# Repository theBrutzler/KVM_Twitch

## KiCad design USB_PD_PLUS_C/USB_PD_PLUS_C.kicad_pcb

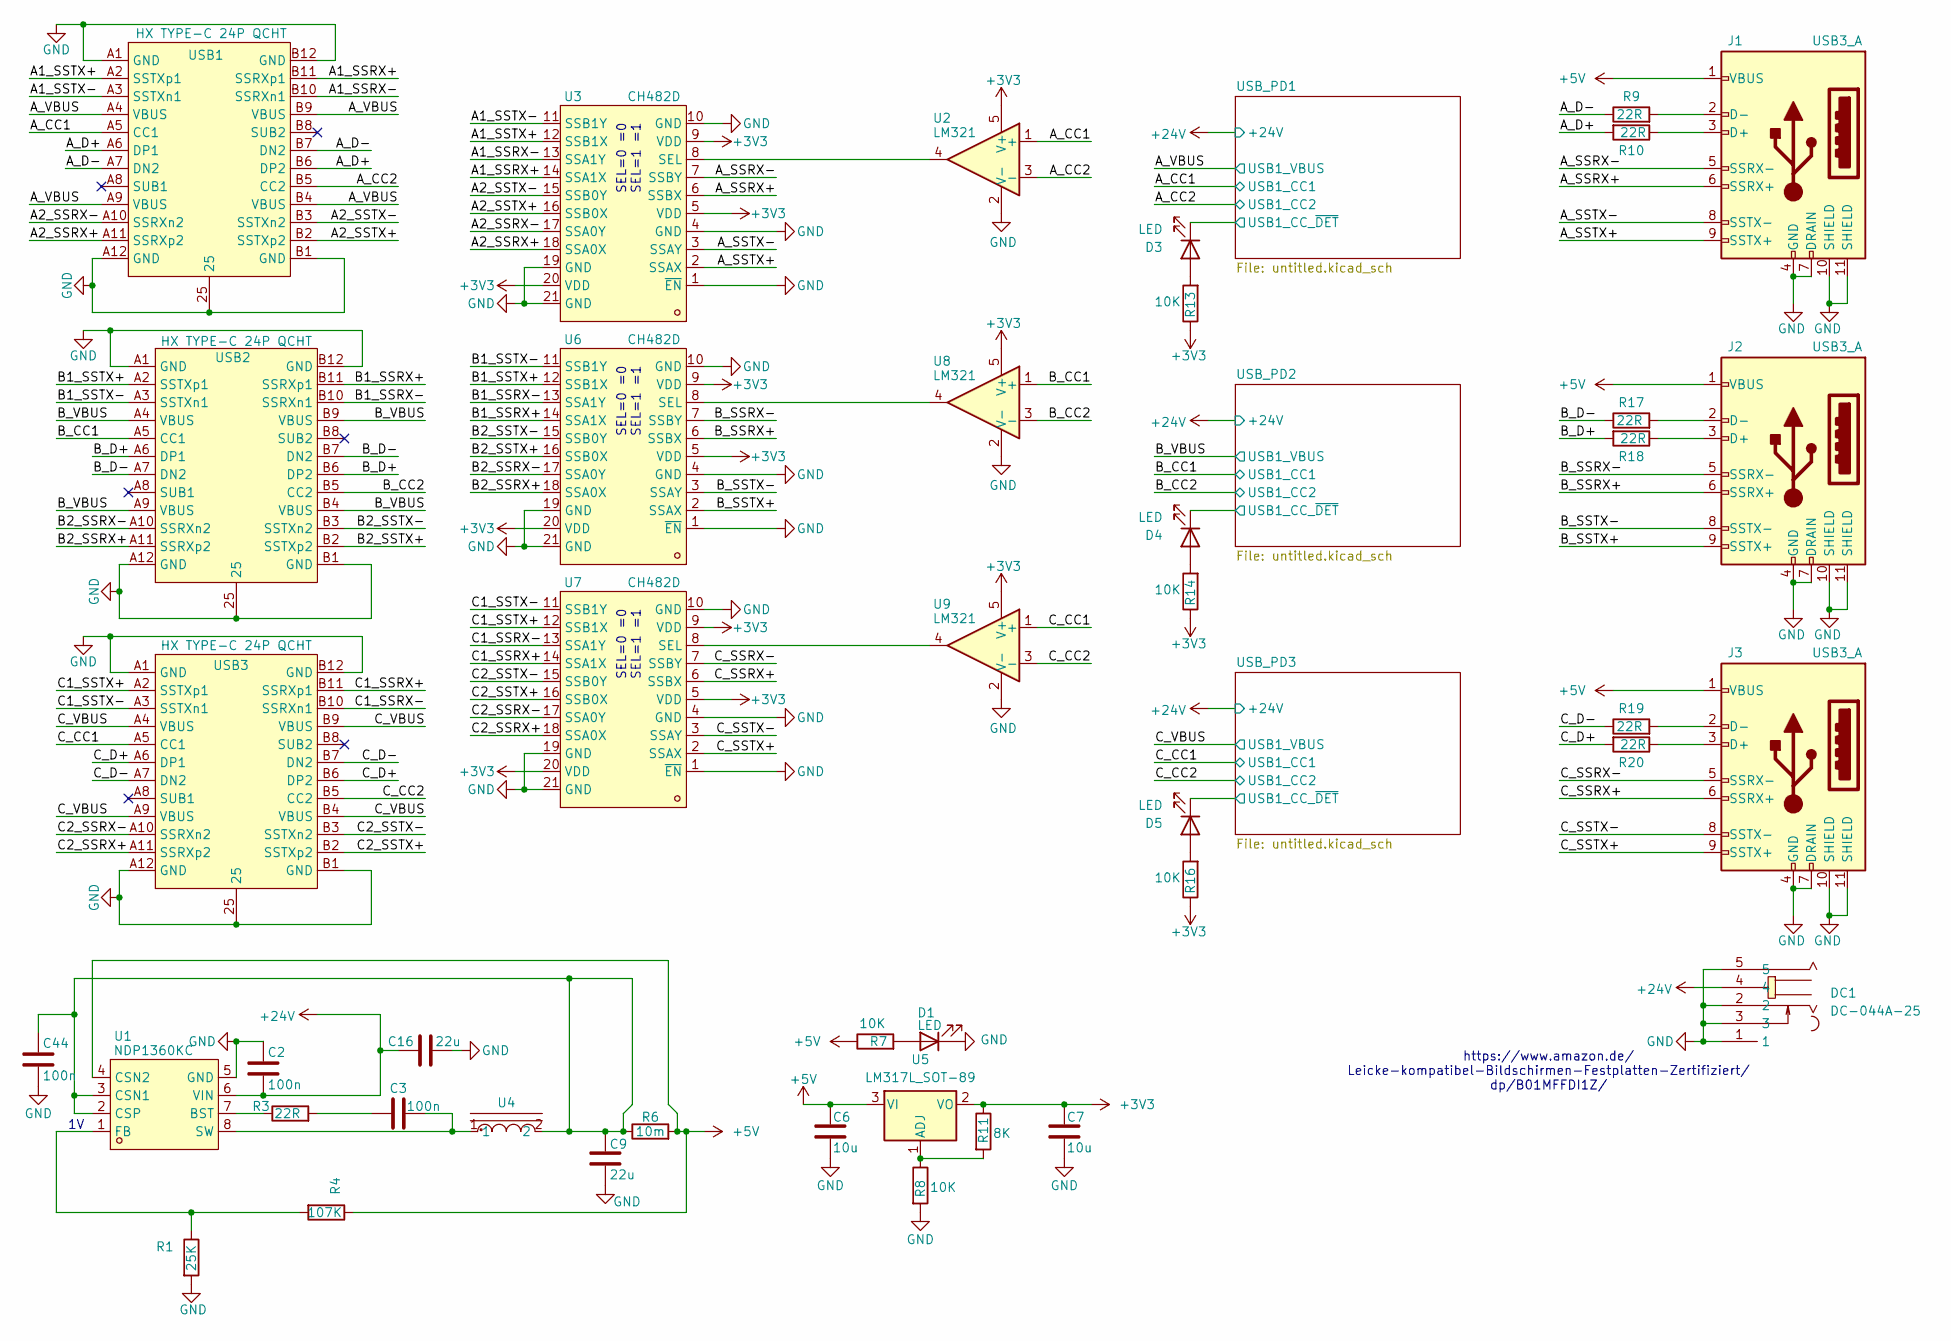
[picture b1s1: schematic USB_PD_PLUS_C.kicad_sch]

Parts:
C2, C3, C44: 100n; C_0402_1005Metric; LCSC C5142567
C6, C7: 10u; C_0603_1608Metric; LCSC C6119842
C9, C16: 22u; C1812; LCSC Part C22388553
D1, D3, D4, D5: LED; LED_0603_1608Metric; LCSC C7496819
DC1: DC-044A-25; DC-IN-TH_DC-044A-25A; LCSC Part C22435685
J1, J2, J3: USB3_A; USB-3.0-A-TH_HC-ST-003-01-Z; LCSC Part C2845330
R1: 25K; R_0402_1005Metric; LCSC C273695
R3, R9, R10, R17, R18, R19, R20: 22R; R_0402_1005Metric; LCSC C3017454
R4: 107K; R_0402_1005Metric; LCSC C3017514
R6: 10m; R_1206_3216Metric; LCSC Part C42454021
R7, R8, R13, R14, R16: 10K; R_0402_1005Metric; LCSC C102759
R11: 8K; R_0402_1005Metric; LCSC C2960789
U1: NDP1360KC; SOP-8_L4.9-W3.9-P1.27-LS6.0-BL; LCSC Part C7420576
U2, U8, U9: LM321; SOT-23-5; LCSC C53413338
U3, U6, U7: CH482D; VFQFN-20_L4.5-W2.5-P0.5-BL-EP; LCSC Part C2913009
U4: CXP0650-220M-AG(22UH); IND-SMD_L7.1-W6.6_CXP0650; LCSC Part C7187321
U5: LM317L_SOT-89; SOT-89-3; LCSC C45953613
USB1, USB2, USB3: HX TYPE-C 24P QCHT; TYPE-C-SMD_TYPE-C-24P-QCHT; LCSC Part C5178545

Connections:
+3V3: C7.1, R11.1, R13.1, R14.1, R16.1, U2.5 (V+), U3.5 (VDD), U3.9 (VDD), U3.20 (VDD), U5.2 (VO), U6.5 (VDD), U6.9 (VDD), U6.20 (VDD), U7.5 (VDD), U7.9 (VDD), U7.20 (VDD), U8.5 (V+), U9.5 (V+)
+5V: C6.1, J1.1 (VBUS), J2.1 (VBUS), J3.1 (VBUS), R4.1, R6.2, R7.1, U1.4 (CSN2), U5.3 (VI)
+24V: C2.2, C16.1, DC1.4, U1.6 (VIN); also elsewhere on the board
/A1_SSRX+: U3.14 (SSA1X), USB1.B11 (SSRXp1)
/A1_SSRX-: U3.13 (SSA1Y), USB1.B10 (SSRXn1)
/A1_SSTX+: U3.12 (SSB1X), USB1.A2 (SSTXp1)
/A1_SSTX-: U3.11 (SSB1Y), USB1.A3 (SSTXn1)
/A2_SSRX+: U3.18 (SSA0X), USB1.A11 (SSRXp2)
/A2_SSRX-: U3.17 (SSA0Y), USB1.A10 (SSRXn2)
/A2_SSTX+: U3.16 (SSB0X), USB1.B2 (SSTXp2)
/A2_SSTX-: U3.15 (SSB0Y), USB1.B3 (SSTXn2)
/A_CC1: U2.1 (+), USB1.A5 (CC1); also elsewhere on the board
/A_CC2: U2.3 (-), USB1.B5 (CC2); also elsewhere on the board
/A_D+: R10.2, USB1.A6 (DP1), USB1.B6 (DP2)
/A_D-: R9.1, USB1.A7 (DN2), USB1.B7 (DN2)
/A_SSRX+: J1.6 (SSRX+), U3.6 (SSBX)
/A_SSRX-: J1.5 (SSRX-), U3.7 (SSBY)
/A_SSTX+: J1.9 (SSTX+), U3.2 (SSAX)
/A_SSTX-: J1.8 (SSTX-), U3.3 (SSAY)
/A_VBUS: USB1.A4 (VBUS), USB1.A9 (VBUS), USB1.B4 (VBUS), USB1.B9 (VBUS); also elsewhere on the board
/B1_SSRX+: U6.14 (SSA1X), USB2.B11 (SSRXp1)
/B1_SSRX-: U6.13 (SSA1Y), USB2.B10 (SSRXn1)
/B1_SSTX+: U6.12 (SSB1X), USB2.A2 (SSTXp1)
/B1_SSTX-: U6.11 (SSB1Y), USB2.A3 (SSTXn1)
/B2_SSRX+: U6.18 (SSA0X), USB2.A11 (SSRXp2)
/B2_SSRX-: U6.17 (SSA0Y), USB2.A10 (SSRXn2)
/B2_SSTX+: U6.16 (SSB0X), USB2.B2 (SSTXp2)
/B2_SSTX-: U6.15 (SSB0Y), USB2.B3 (SSTXn2)
/B_CC1: U8.1 (+), USB2.A5 (CC1); also elsewhere on the board
/B_CC2: U8.3 (-), USB2.B5 (CC2); also elsewhere on the board
/B_D+: R18.2, USB2.A6 (DP1), USB2.B6 (DP2)
/B_D-: R17.1, USB2.A7 (DN2), USB2.B7 (DN2)
/B_SSRX+: J2.6 (SSRX+), U6.6 (SSBX)
/B_SSRX-: J2.5 (SSRX-), U6.7 (SSBY)
/B_SSTX+: J2.9 (SSTX+), U6.2 (SSAX)
/B_SSTX-: J2.8 (SSTX-), U6.3 (SSAY)
/B_VBUS: USB2.A4 (VBUS), USB2.A9 (VBUS), USB2.B4 (VBUS), USB2.B9 (VBUS); also elsewhere on the board
/C1_SSRX+: U7.14 (SSA1X), USB3.B11 (SSRXp1)
/C1_SSRX-: U7.13 (SSA1Y), USB3.B10 (SSRXn1)
/C1_SSTX+: U7.12 (SSB1X), USB3.A2 (SSTXp1)
/C1_SSTX-: U7.11 (SSB1Y), USB3.A3 (SSTXn1)
/C2_SSRX+: U7.18 (SSA0X), USB3.A11 (SSRXp2)
/C2_SSRX-: U7.17 (SSA0Y), USB3.A10 (SSRXn2)
/C2_SSTX+: U7.16 (SSB0X), USB3.B2 (SSTXp2)
/C2_SSTX-: U7.15 (SSB0Y), USB3.B3 (SSTXn2)
/C_CC1: U9.1 (+), USB3.A5 (CC1); also elsewhere on the board
/C_CC2: U9.3 (-), USB3.B5 (CC2); also elsewhere on the board
/C_D+: R20.2, USB3.A6 (DP1), USB3.B6 (DP2)
/C_D-: R19.1, USB3.A7 (DN2), USB3.B7 (DN2)
/C_SSRX+: J3.6 (SSRX+), U7.6 (SSBX)
/C_SSRX-: J3.5 (SSRX-), U7.7 (SSBY)
/C_SSTX+: J3.9 (SSTX+), U7.2 (SSAX)
/C_SSTX-: J3.8 (SSTX-), U7.3 (SSAY)
/C_VBUS: USB3.A4 (VBUS), USB3.A9 (VBUS), USB3.B4 (VBUS), USB3.B9 (VBUS); also elsewhere on the board
/USB_PD1/USB1_CC_~DET: D3.1 (K); also elsewhere on the board
/USB_PD2/USB1_CC_~DET: D4.1 (K); also elsewhere on the board
/USB_PD3/USB1_CC_~DET: D5.1 (K); also elsewhere on the board
GND: C2.1, C6.2, C7.2, C9.2, C16.2, C44.2, D1.1 (K), DC1.1, DC1.2, DC1.3, DC1.5, J1.4 (GND), J1.7 (DRAIN), J1.10 (SHIELD), J1.11 (SHIELD), J2.4 (GND), J2.7 (DRAIN), J2.10 (SHIELD), J2.11 (SHIELD), J3.4 (GND), J3.7 (DRAIN), J3.10 (SHIELD), J3.11 (SHIELD), R1.2, R8.2, U1.5 (GND), U2.2 (V-), U3.1 (~EN), U3.4 (GND), U3.10 (GND), U3.19 (GND), U3.21 (GND), U6.1 (~EN), U6.4 (GND), U6.10 (GND), U6.19 (GND), U6.21 (GND), U7.1 (~EN), U7.4 (GND), U7.10 (GND), U7.19 (GND), U7.21 (GND), U8.2 (V-), U9.2 (V-), USB1.25, USB1.A1 (GND), USB1.A12 (GND), USB1.B1 (GND), USB1.B12 (GND), USB2.25, USB2.A1 (GND), USB2.A12 (GND), USB2.B1 (GND), USB2.B12 (GND), USB3.25, USB3.A1 (GND), USB3.A12 (GND), USB3.B1 (GND), USB3.B12 (GND); also elsewhere on the board
unnamed: C3.1, R3.2
unnamed: D1.2 (A), R7.2
unnamed: D3.2 (A), R13.2
unnamed: D4.2 (A), R14.2
unnamed: D5.2 (A), R16.2
unnamed: J1.3 (D+), R10.1
unnamed: J1.2 (D-), R9.2
unnamed: J2.3 (D+), R18.1
unnamed: J2.2 (D-), R17.2
unnamed: J3.3 (D+), R20.1
unnamed: J3.2 (D-), R19.2
unnamed: R3.1, U1.7 (BST)
unnamed: C9.1, C44.1, R6.1, U1.2 (CSP), U1.3 (CSN1), U4.2
unnamed: R1.1, R4.2, U1.1 (FB)
unnamed: C3.2, U1.8 (SW), U4.1
unnamed: U2.4, U3.8 (SEL)
unnamed: R8.1, R11.2, U5.1 (ADJ)
unnamed: U6.8 (SEL), U8.4
unnamed: U7.8 (SEL), U9.4

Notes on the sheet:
SEL=0 =0 SEL=1 =1
https://www.amazon.de/ Leicke-kompatibel-Bildschirmen-Festplatten-Zertifiziert/ dp/B01MFFDI1Z/

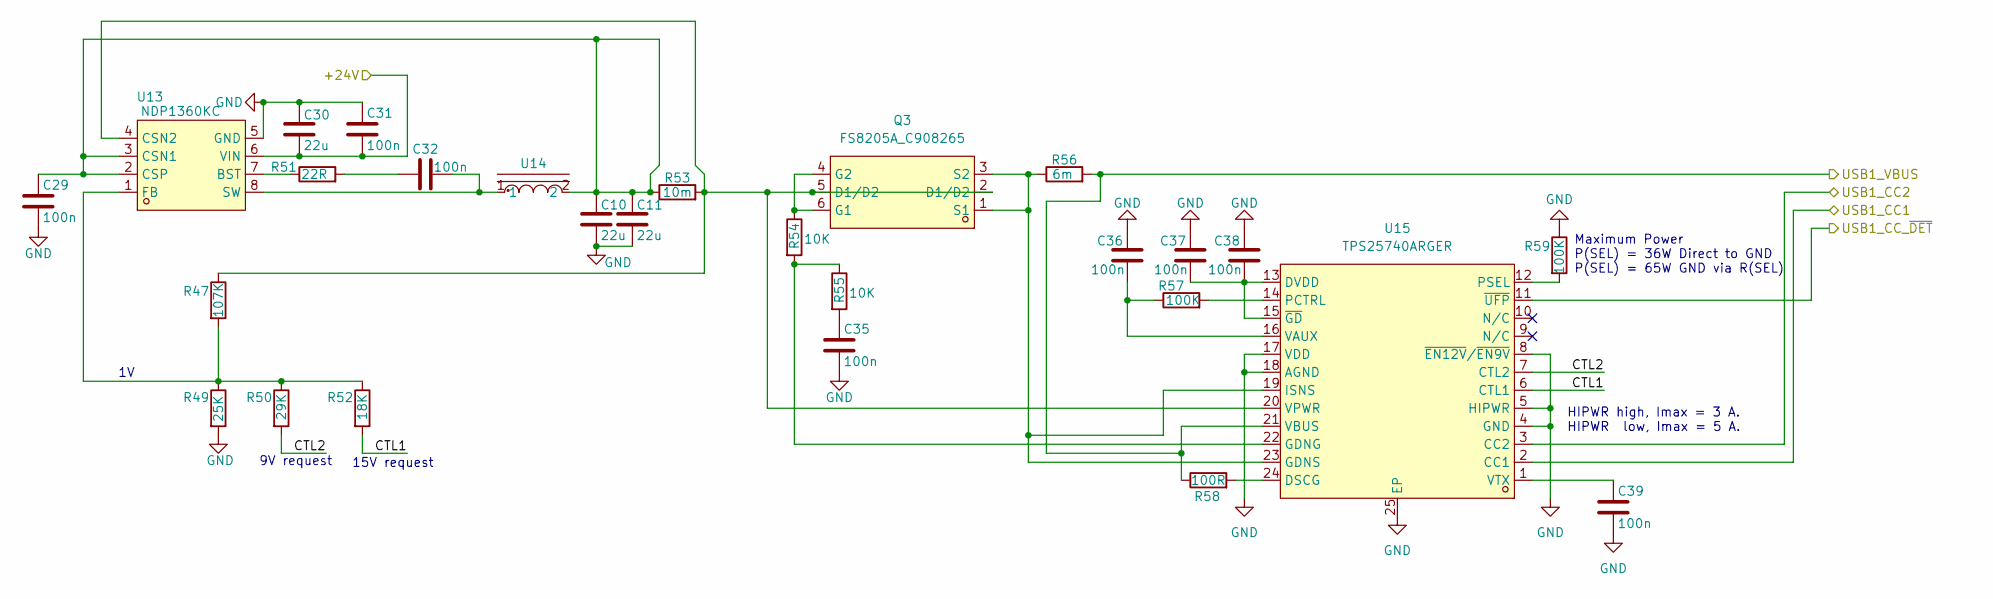
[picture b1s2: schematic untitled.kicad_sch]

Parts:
C10, C11, C30: 22u; C1812; LCSC Part C22388553
C29, C31, C32, C35, C36, C37, C38, C39: 100n; C_0402_1005Metric; LCSC C5142567
Q3: FS8205A_C908265; SOT-23-6_L2.9-W1.6-P0.95-LS2.8-BR; MPN FS8205A; LCSC Part C908265
R47: 107K; R_0402_1005Metric; LCSC C25743
R49: 25K; R_0402_1005Metric; LCSC C273695
R50: 29K; R_0402_1005Metric
R51: 22R; R_0402_1005Metric; LCSC C3017454
R52: 18K; R_0402_1005Metric
R53: 10m; R_1206_3216Metric; LCSC Part C42454021
R54, R55: 10K; R_0402_1005Metric; LCSC C102759
R56: 6m; R_1206_3216Metric
R57, R59: 100K; R_0402_1005Metric; LCSC C3017514
R58: 100R; R_0402_1005Metric
U13: NDP1360KC; SOP-8_L4.9-W3.9-P1.27-LS6.0-BL; LCSC Part C7420576
U14: CXP0650-220M-AG(22UH); IND-SMD_L7.1-W6.6_CXP0650; LCSC Part C7187321
U15: TPS25740ARGER; VQFN-24_L4.0-W4.0-P0.50-TL-EP; MPN TPS25740ARGER; LCSC Part C544309

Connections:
+24V: C30.2, C31.2, U13.6 (VIN); also elsewhere on the board
/B_CC1: U15.2 (CC1); also elsewhere on the board
/B_CC2: U15.3 (CC2); also elsewhere on the board
/B_VBUS: R56.2, R58.1, U15.21 (VBUS); also elsewhere on the board
/USB_PD2/CTL1: R52.2, U15.6 (CTL1)
/USB_PD2/CTL2: R50.2, U15.7 (CTL2)
/USB_PD2/USB1_CC_~DET: U15.11 (~UFP); also elsewhere on the board
GND: C10.2, C11.2, C29.2, C30.1, C31.1, C35.2, C36.2, C37.2, C38.2, C39.2, R49.2, R59.1, U13.5 (GND), U15.4 (GND), U15.5 (HIPWR), U15.8 (~EN12V/~EN9V), U15.17 (VDD), U15.18 (AGND), U15.25 (EP); also elsewhere on the board
unnamed: C32.1, R51.2
unnamed: C35.1, R55.2
unnamed: Q3.4 (G2), Q3.6 (G1), R54.1
unnamed: Q3.1 (S1), Q3.3 (S2), R56.1, U15.19 (ISNS), U15.23 (GDNS)
unnamed: R51.1, U13.7 (BST)
unnamed: C10.1, C11.1, C29.1, R53.1, U13.2 (CSP), U13.3 (CSN1), U14.2
unnamed: Q3.2 (D1/D2), Q3.5 (D1/D2), R47.1, R53.2, U13.4 (CSN2), U15.20 (VPWR)
unnamed: R47.2, R49.1, R50.1, R52.1, U13.1 (FB)
unnamed: C32.2, U13.8 (SW), U14.1
unnamed: R58.2, U15.24 (DSCG)
unnamed: C37.1, C38.1, U15.13 (DVDD), U15.15 (~GD)
unnamed: R54.2, R55.1, U15.22 (GDNG)
unnamed: R57.2, U15.14 (PCTRL)
unnamed: R59.2, U15.12 (PSEL)
unnamed: C36.1, R57.1, U15.16 (VAUX)
unnamed: C39.1, U15.1 (VTX)

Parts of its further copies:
C12, C13, C14, C15, C18, C41: 22u; C1812; LCSC Part C22388553
C19, C20, C23, C24, C25, C26, C27, C28, C40, C42, C43, C46, C47, C48, C49, C50: 100n; C_0402_1005Metric; LCSC C5142567
Q2, Q4: FS8205A_C908265; SOT-23-6_L2.9-W1.6-P0.95-LS2.8-BR; MPN FS8205A; LCSC Part C908265
R34, R60: 107K; R_0402_1005Metric; LCSC C25743
R36, R62: 25K; R_0402_1005Metric; LCSC C273695
R37, R63: 29K; R_0402_1005Metric
R38, R64: 22R; R_0402_1005Metric; LCSC C3017454
R39, R65: 18K; R_0402_1005Metric
R40, R66: 10m; R_1206_3216Metric; LCSC Part C42454021
R41, R42, R67, R68: 10K; R_0402_1005Metric; LCSC C102759
R43, R69: 6m; R_1206_3216Metric
R44, R46, R70, R72: 100K; R_0402_1005Metric; LCSC C3017514
R45, R71: 100R; R_0402_1005Metric
U10, U16: NDP1360KC; SOP-8_L4.9-W3.9-P1.27-LS6.0-BL; LCSC Part C7420576
U11, U17: CXP0650-220M-AG(22UH); IND-SMD_L7.1-W6.6_CXP0650; LCSC Part C7187321
U12, U18: TPS25740ARGER; VQFN-24_L4.0-W4.0-P0.50-TL-EP; MPN TPS25740ARGER; LCSC Part C544309

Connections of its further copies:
+24V: C18.2, C19.2, C41.2, C42.2, U10.6 (VIN), U16.6 (VIN); also elsewhere on the board
/A_CC1: U12.2 (CC1); also elsewhere on the board
/A_CC2: U12.3 (CC2); also elsewhere on the board
/A_VBUS: R43.2, R45.1, U12.21 (VBUS); also elsewhere on the board
/C_CC1: U18.2 (CC1); also elsewhere on the board
/C_CC2: U18.3 (CC2); also elsewhere on the board
/C_VBUS: R69.2, R71.1, U18.21 (VBUS); also elsewhere on the board
/USB_PD1/CTL1: R39.2, U12.6 (CTL1)
/USB_PD1/CTL2: R37.2, U12.7 (CTL2)
/USB_PD1/USB1_CC_~DET: U12.11 (~UFP); also elsewhere on the board
/USB_PD3/CTL1: R65.2, U18.6 (CTL1)
/USB_PD3/CTL2: R63.2, U18.7 (CTL2)
/USB_PD3/USB1_CC_~DET: U18.11 (~UFP); also elsewhere on the board
GND: C12.2, C13.2, C14.2, C15.2, C18.1, C19.1, C23.2, C24.2, C25.2, C26.2, C27.2, C28.2, C40.2, C41.1, C42.1, C46.2, C47.2, C48.2, C49.2, C50.2, R36.2, R46.1, R62.2, R72.1, U10.5 (GND), U12.4 (GND), U12.5 (HIPWR), U12.8 (~EN12V/~EN9V), U12.17 (VDD), U12.18 (AGND), U12.25 (EP), U16.5 (GND), U18.4 (GND), U18.5 (HIPWR), U18.8 (~EN12V/~EN9V), U18.17 (VDD), U18.18 (AGND), U18.25 (EP); also elsewhere on the board
unnamed: C20.1, R38.2
unnamed: C23.1, R42.2
unnamed: C43.1, R64.2
unnamed: C46.1, R68.2
unnamed: Q2.4 (G2), Q2.6 (G1), R41.1
unnamed: Q2.1 (S1), Q2.3 (S2), R43.1, U12.19 (ISNS), U12.23 (GDNS)
unnamed: Q4.4 (G2), Q4.6 (G1), R67.1
unnamed: Q4.1 (S1), Q4.3 (S2), R69.1, U18.19 (ISNS), U18.23 (GDNS)
unnamed: R38.1, U10.7 (BST)
unnamed: C12.1, C13.1, C28.1, R40.1, U10.2 (CSP), U10.3 (CSN1), U11.2
unnamed: Q2.2 (D1/D2), Q2.5 (D1/D2), R34.1, R40.2, U10.4 (CSN2), U12.20 (VPWR)
unnamed: R34.2, R36.1, R37.1, R39.1, U10.1 (FB)
unnamed: C20.2, U10.8 (SW), U11.1
unnamed: R45.2, U12.24 (DSCG)
unnamed: C25.1, C26.1, U12.13 (DVDD), U12.15 (~GD)
unnamed: R41.2, R42.1, U12.22 (GDNG)
unnamed: R44.2, U12.14 (PCTRL)
unnamed: R46.2, U12.12 (PSEL)
unnamed: C24.1, R44.1, U12.16 (VAUX)
unnamed: C27.1, U12.1 (VTX)
unnamed: R64.1, U16.7 (BST)
unnamed: C14.1, C15.1, C40.1, R66.1, U16.2 (CSP), U16.3 (CSN1), U17.2
unnamed: Q4.2 (D1/D2), Q4.5 (D1/D2), R60.1, R66.2, U16.4 (CSN2), U18.20 (VPWR)
unnamed: R60.2, R62.1, R63.1, R65.1, U16.1 (FB)
unnamed: C43.2, U16.8 (SW), U17.1
unnamed: R71.2, U18.24 (DSCG)
unnamed: C48.1, C49.1, U18.13 (DVDD), U18.15 (~GD)
unnamed: R67.2, R68.1, U18.22 (GDNG)
unnamed: R70.2, U18.14 (PCTRL)
unnamed: R72.2, U18.12 (PSEL)
unnamed: C47.1, R70.1, U18.16 (VAUX)
unnamed: C50.1, U18.1 (VTX)

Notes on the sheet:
9V request
Maximum Power P(SEL) = 36W Direct to GND P(SEL) = 65W GND via R(SEL)
HIPWR high, Imax = 3 A. HIPWR low, Imax = 5 A.
15V request

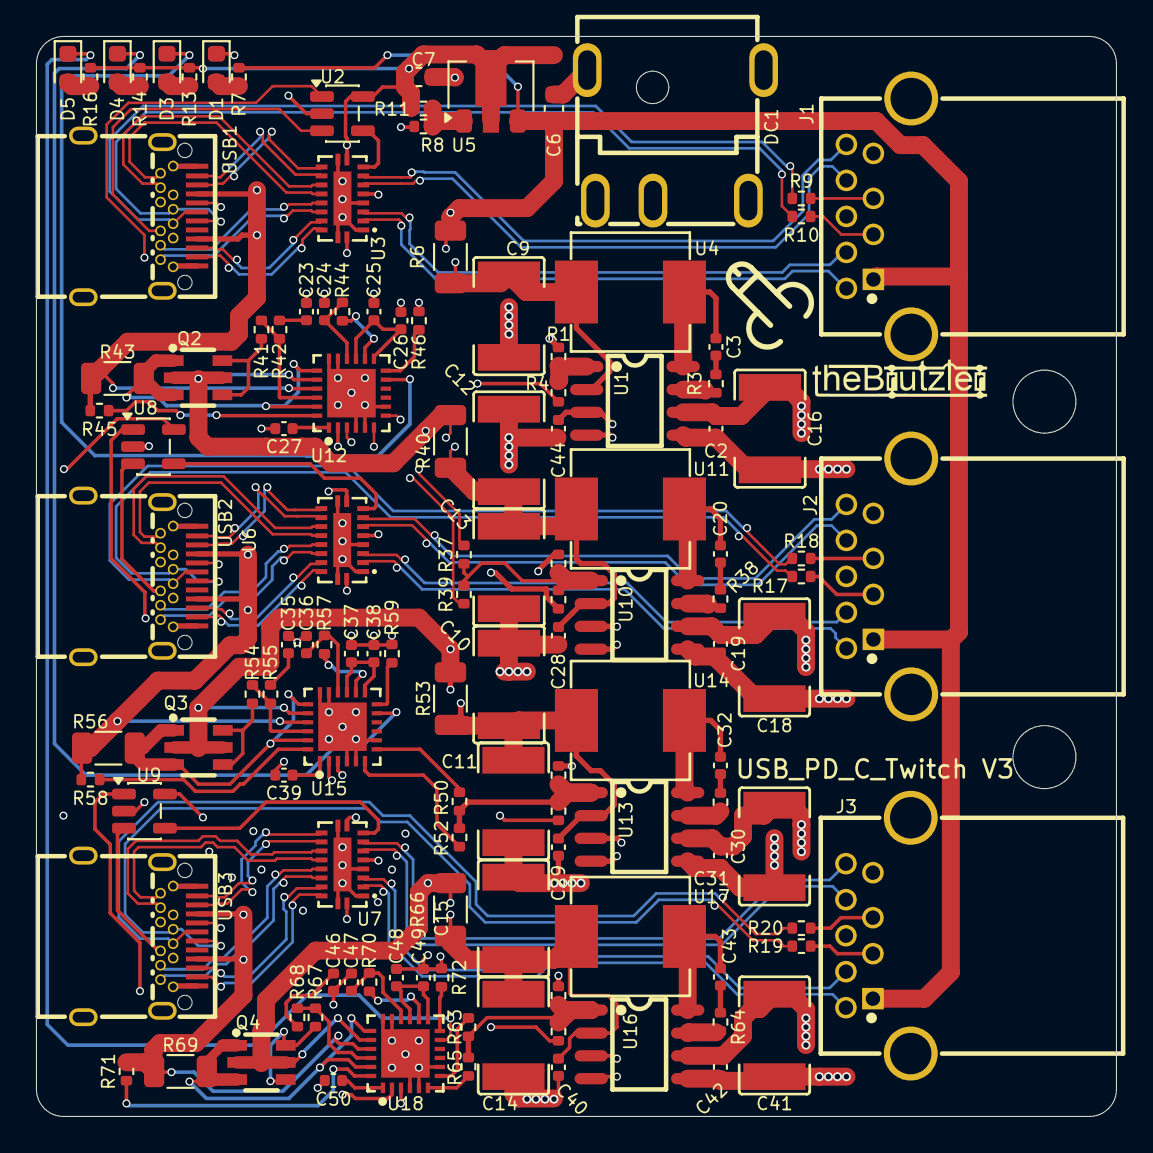
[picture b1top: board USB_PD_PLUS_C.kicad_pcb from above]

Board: 4 copper layers, 60.0 x 60.0 mm, 124 parts (0 on the bottom side), 131 nets.

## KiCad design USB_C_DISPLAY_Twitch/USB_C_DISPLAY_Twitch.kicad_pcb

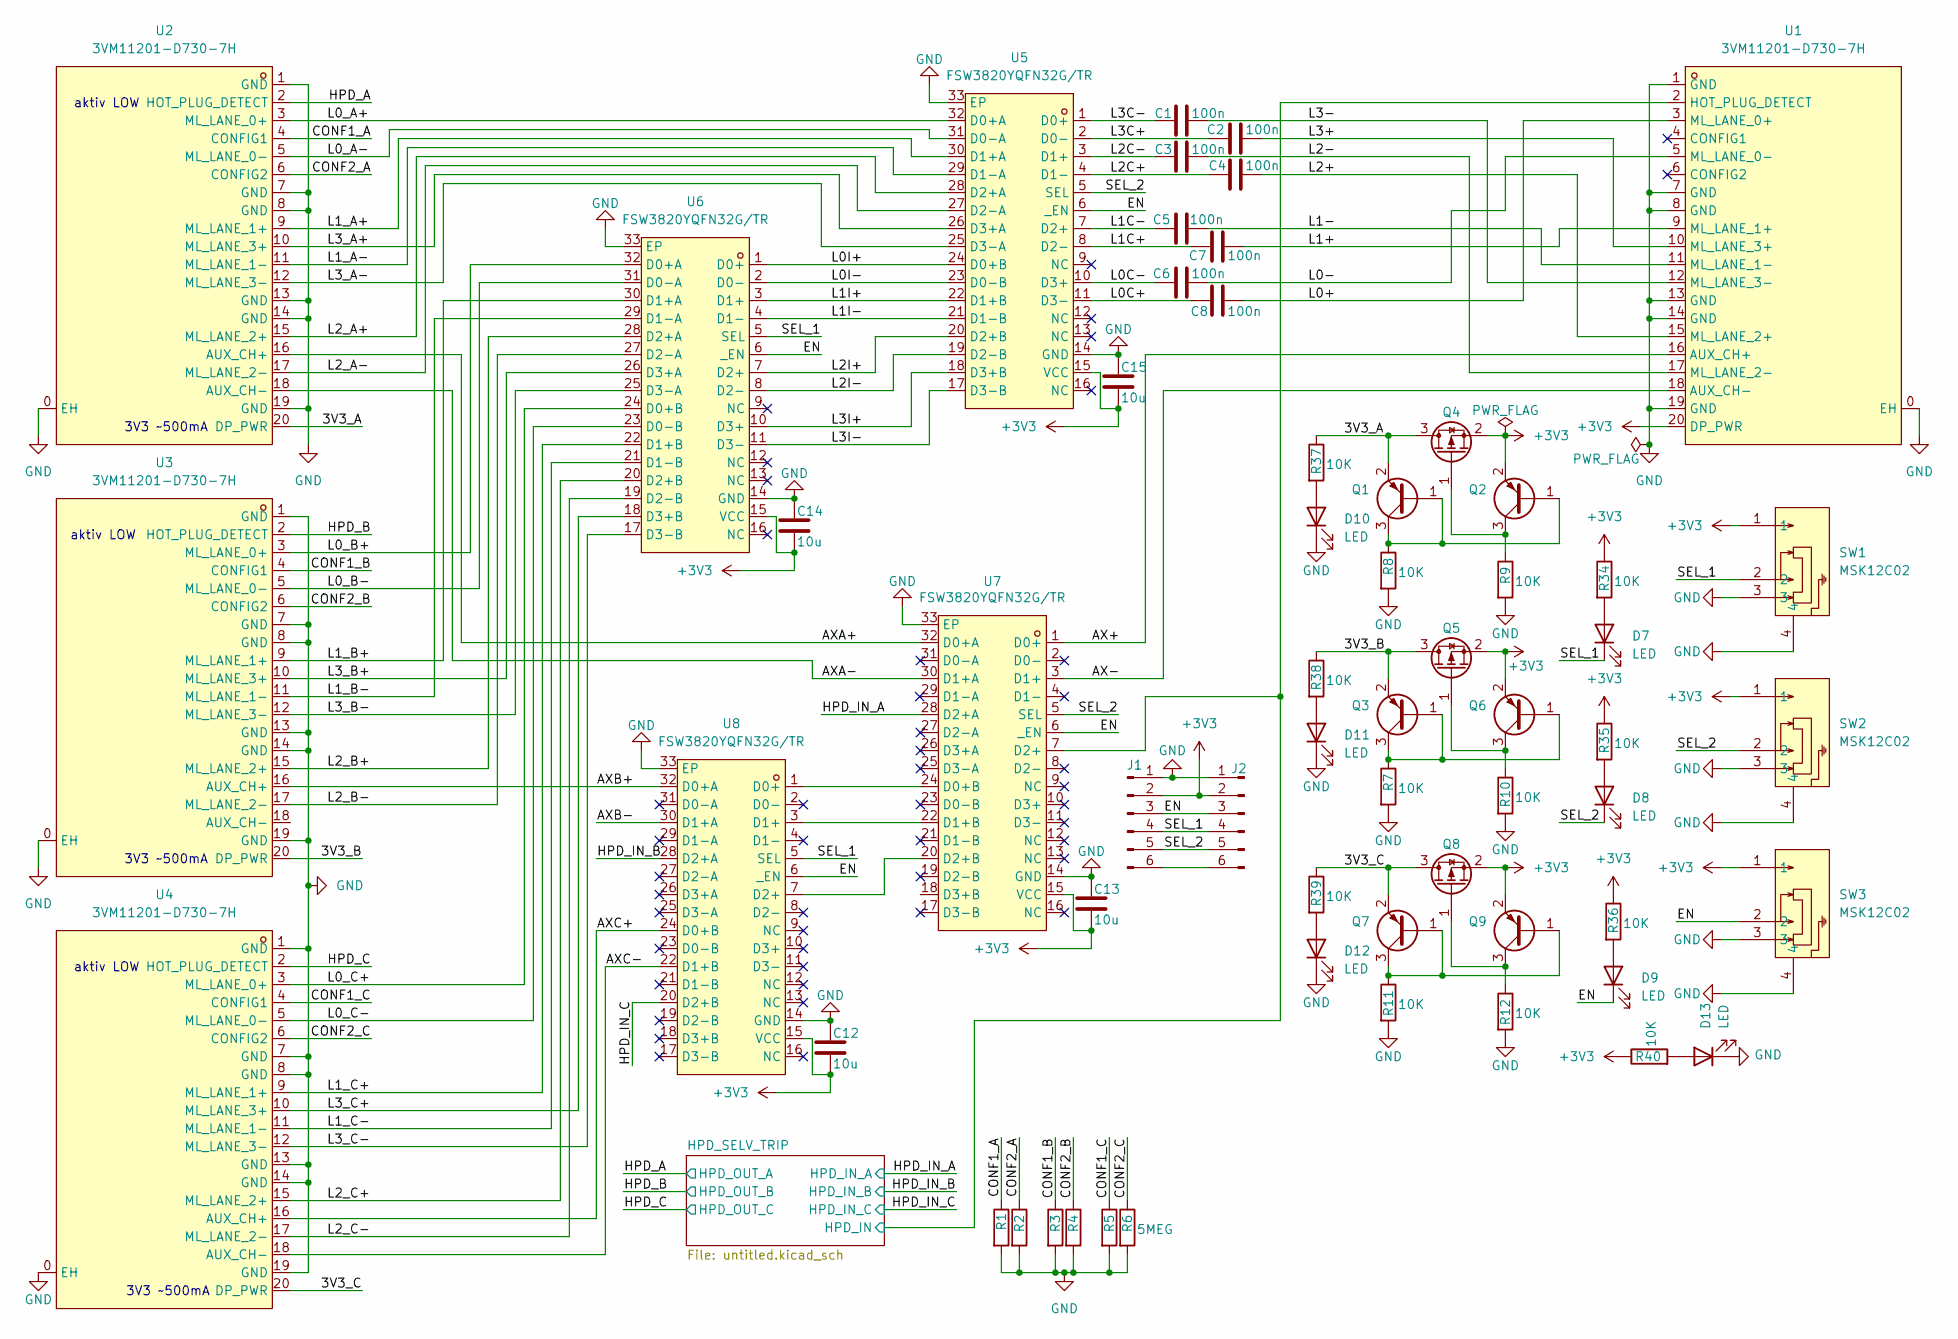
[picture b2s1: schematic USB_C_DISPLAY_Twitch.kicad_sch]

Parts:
C1, C2, C3, C4, C5, C6, C7, C8: 100n; C_0402_1005Metric; LCSC C344189
C12, C13, C14, C15: 10u; C_0603_1608Metric; LCSC C6119842
D7, D8, D9, D10, D11, D12, D13: LED; LED_0603_1608Metric; LCSC C7496819
J1, J2: Conn_01x06_Pin; JST_XH_B6B-XH-AM_1x06_P2.50mm_Vertical; LCSC C144397
Q1, Q2, Q3, Q6, Q7, Q9: Q_PNP_BEC; SOT-23-3_L2.9-W1.3-P1.90-LS2.4-BR; LCSC C2891805
Q4, Q5, Q8: Q_PMOS_GSD; SOT-23; LCSC C41384537
R1, R2, R3, R4, R5, R6: 5MEG; R_0402_1005Metric; LCSC C3017614
R7, R8, R9, R10, R11, R12, R34, R35, R36, R37, R38, R39, R40: 10K; R_0402_1005Metric; LCSC C102759
SW1, SW2, SW3: MSK12C02; SW-TH_MSK12C02; LCSC Part C431540
U1, U2, U3, U4: 3VM11201-D730-7H; CONN-SMD_3VM11201-D730-7H; LCSC Part C2895506
U5, U6, U7, U8: FSW3820YQFN32G/TR; QFN-32_L4.0-W4.0-P0.40-TL-EP2.9; LCSC Part C32713321

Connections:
+3V3: C12.2, C13.2, C14.2, C15.2, J1.2, J2.2, Q2.2 (E), Q4.2 (S), Q5.2 (S), Q6.2 (E), Q8.2 (S), Q9.2 (E), R34.1, R35.1, R36.1, R40.1, SW1.1, SW2.1, SW3.1, U1.20 (DP_PWR), U5.15 (VCC), U6.15 (VCC), U7.15 (VCC), U8.15 (VCC); also elsewhere on the board
/3V3_A: Q1.2 (E), Q4.3 (D), R37.1, U2.20 (DP_PWR)
/3V3_B: Q3.2 (E), Q5.3 (D), R38.1, U3.20 (DP_PWR)
/3V3_C: Q7.2 (E), Q8.3 (D), R39.1, U4.20 (DP_PWR)
/AX+: U1.16 (AUX_CH+), U7.1 (D0+)
/AX-: U1.18 (AUX_CH-), U7.3 (D1+)
/AXA+: U2.16 (AUX_CH+), U7.32 (D0+A)
/AXA-: U2.18 (AUX_CH-), U7.30 (D1+A)
/AXB+: U3.16 (AUX_CH+), U8.32 (D0+A)
/AXB-: U8.30 (D1+A)
/AXC+: U4.16 (AUX_CH+), U8.24 (D0+B)
/AXC-: U4.18 (AUX_CH-), U8.22 (D1+B)
/CONF1_A: R1.1, U2.4 (CONFIG1)
/CONF1_B: R3.1, U3.4 (CONFIG1)
/CONF1_C: R5.1, U4.4 (CONFIG1)
/CONF2_A: R2.1, U2.6 (CONFIG2)
/CONF2_B: R4.1, U3.6 (CONFIG2)
/CONF2_C: R6.1, U4.6 (CONFIG2)
/EN: D9.1 (K), J1.3, J2.3, SW3.2, U5.6 (_EN), U6.6 (_EN), U7.6 (_EN), U8.6 (_EN)
/HPD_A: U2.2 (HOT_PLUG_DETECT); also elsewhere on the board
/HPD_B: U3.2 (HOT_PLUG_DETECT); also elsewhere on the board
/HPD_C: U4.2 (HOT_PLUG_DETECT); also elsewhere on the board
/HPD_IN_A: U7.28 (D2+A); also elsewhere on the board
/HPD_IN_B: U8.28 (D2+A); also elsewhere on the board
/HPD_IN_C: U8.20 (D2+B); also elsewhere on the board
/HPD_SELV_TRIP/HPD_IN: U1.2 (HOT_PLUG_DETECT), U7.7 (D2+); also elsewhere on the board
/L0+: C8.2, U1.3 (ML_LANE_0+)
/L0-: C6.2, U1.5 (ML_LANE_0-)
/L0C+: C8.1, U5.11 (D3-)
/L0C-: C6.1, U5.10 (D3+)
/L0I+: U5.24 (D0+B), U6.1 (D0+)
/L0I-: U5.23 (D0-B), U6.2 (D0-)
/L0_A+: U2.3 (ML_LANE_0+), U5.32 (D0+A)
/L0_A-: U2.5 (ML_LANE_0-), U5.31 (D0-A)
/L0_B+: U3.3 (ML_LANE_0+), U6.32 (D0+A)
/L0_B-: U3.5 (ML_LANE_0-), U6.31 (D0-A)
/L0_C+: U4.3 (ML_LANE_0+), U6.24 (D0+B)
/L0_C-: U4.5 (ML_LANE_0-), U6.23 (D0-B)
/L1+: C7.2, U1.9 (ML_LANE_1+)
/L1-: C5.2, U1.11 (ML_LANE_1-)
/L1C+: C7.1, U5.8 (D2-)
/L1C-: C5.1, U5.7 (D2+)
/L1I+: U5.22 (D1+B), U6.3 (D1+)
/L1I-: U5.21 (D1-B), U6.4 (D1-)
/L1_A+: U2.9 (ML_LANE_1+), U5.30 (D1+A)
/L1_A-: U2.11 (ML_LANE_1-), U5.29 (D1-A)
/L1_B+: U3.9 (ML_LANE_1+), U6.30 (D1+A)
/L1_B-: U3.11 (ML_LANE_1-), U6.29 (D1-A)
/L1_C+: U4.9 (ML_LANE_1+), U6.22 (D1+B)
/L1_C-: U4.11 (ML_LANE_1-), U6.21 (D1-B)
/L2+: C4.2, U1.15 (ML_LANE_2+)
/L2-: C3.2, U1.17 (ML_LANE_2-)
/L2C+: C4.1, U5.4 (D1-)
/L2C-: C3.1, U5.3 (D1+)
/L2I+: U5.20 (D2+B), U6.7 (D2+)
/L2I-: U5.19 (D2-B), U6.8 (D2-)
/L2_A+: U2.15 (ML_LANE_2+), U5.28 (D2+A)
/L2_A-: U2.17 (ML_LANE_2-), U5.27 (D2-A)
/L2_B+: U3.15 (ML_LANE_2+), U6.28 (D2+A)
/L2_B-: U3.17 (ML_LANE_2-), U6.27 (D2-A)
/L2_C+: U4.15 (ML_LANE_2+), U6.20 (D2+B)
/L2_C-: U4.17 (ML_LANE_2-), U6.19 (D2-B)
/L3+: C2.2, U1.10 (ML_LANE_3+)
/L3-: C1.2, U1.12 (ML_LANE_3-)
/L3C+: C2.1, U5.2 (D0-)
/L3C-: C1.1, U5.1 (D0+)
/L3I+: U5.18 (D3+B), U6.10 (D3+)
/L3I-: U5.17 (D3-B), U6.11 (D3-)
/L3_A+: U2.10 (ML_LANE_3+), U5.26 (D3+A)
/L3_A-: U2.12 (ML_LANE_3-), U5.25 (D3-A)
/L3_B+: U3.10 (ML_LANE_3+), U6.26 (D3+A)
/L3_B-: U3.12 (ML_LANE_3-), U6.25 (D3-A)
/L3_C+: U4.10 (ML_LANE_3+), U6.18 (D3+B)
/L3_C-: U4.12 (ML_LANE_3-), U6.17 (D3-B)
/SEL_1: D7.1 (K), J1.4, J2.4, SW1.2, U6.5 (SEL), U8.5 (SEL)
/SEL_2: D8.1 (K), J1.5, J2.5, SW2.2, U5.5 (SEL), U7.5 (SEL)
GND: C12.1, C13.1, C14.1, C15.1, D10.1 (K), D11.1 (K), D12.1 (K), D13.1 (K), J1.1, J2.1, R1.2, R2.2, R3.2, R4.2, R5.2, R6.2, R7.2, R8.2, R9.2, R10.2, R11.2, R12.2, SW1.3, SW1.4, SW2.3, SW2.4, SW3.3, SW3.4, U1.0 (EH), U1.1 (GND), U1.7 (GND), U1.8 (GND), U1.13 (GND), U1.14 (GND), U1.19 (GND), U2.0 (EH), U2.1 (GND), U2.7 (GND), U2.8 (GND), U2.13 (GND), U2.14 (GND), U2.19 (GND), U3.0 (EH), U3.1 (GND), U3.7 (GND), U3.8 (GND), U3.13 (GND), U3.14 (GND), U3.19 (GND), U4.0 (EH), U4.1 (GND), U4.7 (GND), U4.8 (GND), U4.13 (GND), U4.14 (GND), U4.19 (GND), U5.14 (GND), U5.33 (EP), U6.14 (GND), U6.33 (EP), U7.14 (GND), U7.33 (EP), U8.14 (GND), U8.33 (EP); also elsewhere on the board
unnamed: D7.2 (A), R34.2
unnamed: D8.2 (A), R35.2
unnamed: D9.2 (A), R36.2
unnamed: D10.2 (A), R37.2
unnamed: D11.2 (A), R38.2
unnamed: D12.2 (A), R39.2
unnamed: D13.2 (A), R40.2
unnamed: J1.6, J2.6
unnamed: Q1.1 (B), Q1.3 (C), Q2.1 (B), R8.1
unnamed: Q2.3 (C), Q4.1 (G), R9.1
unnamed: Q3.1 (B), Q3.3 (C), Q6.1 (B), R7.1
unnamed: Q5.1 (G), Q6.3 (C), R10.1
unnamed: Q7.1 (B), Q7.3 (C), Q9.1 (B), R11.1
unnamed: Q8.1 (G), Q9.3 (C), R12.1
unnamed: U7.24 (D0+B), U8.1 (D0+)
unnamed: U7.22 (D1+B), U8.3 (D1+)
unnamed: U7.20 (D2+B), U8.7 (D2+)

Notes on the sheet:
aktiv LOW
3V3 ~500mA

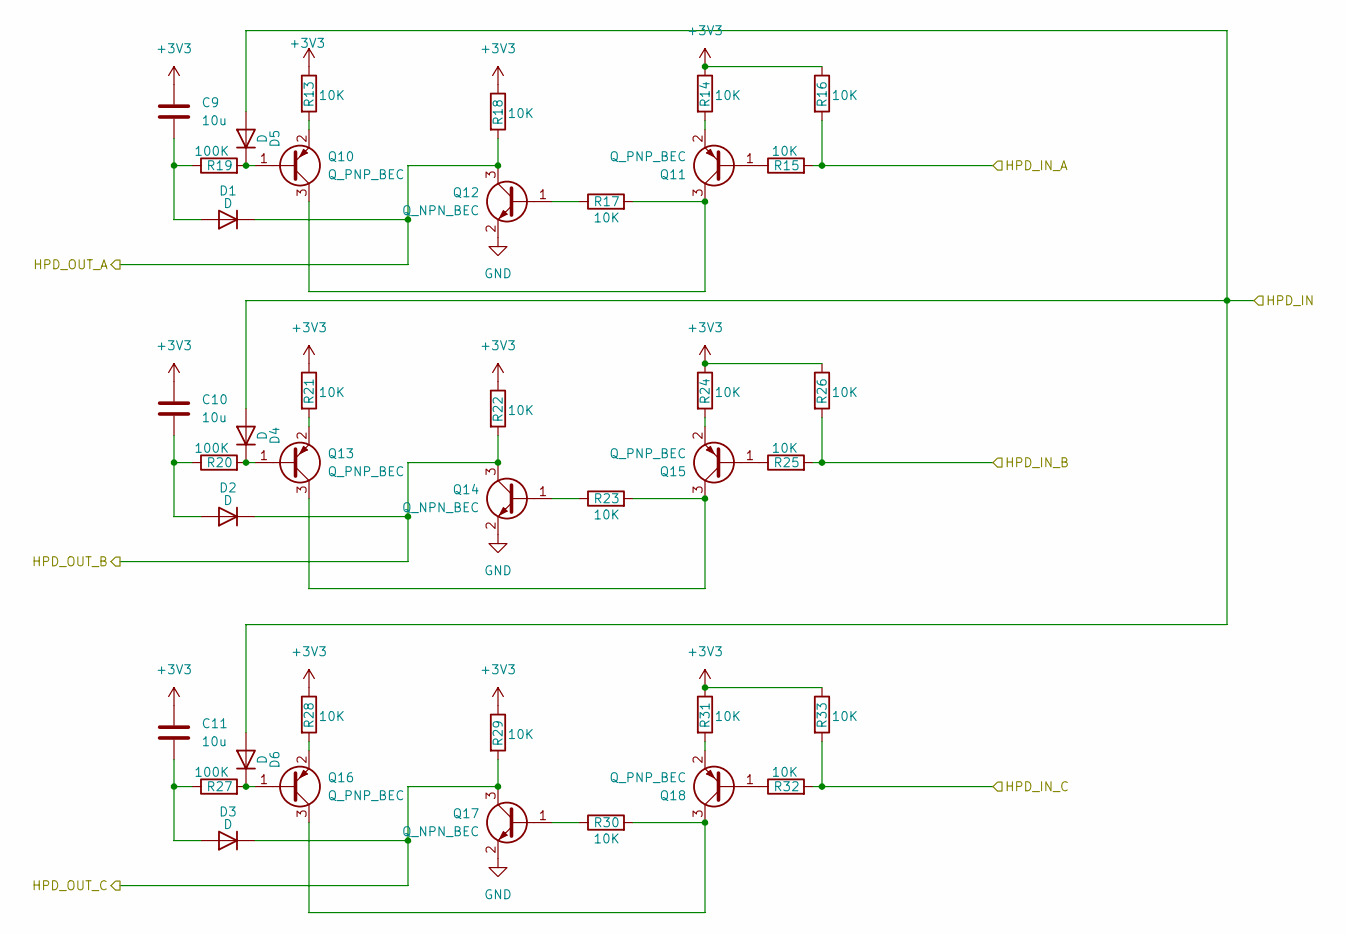
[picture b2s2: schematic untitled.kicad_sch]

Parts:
C9, C10, C11: 10u; C_0603_1608Metric; LCSC C6119842
D1, D2, D3, D4, D5, D6: D; SOD-123FL_L2.8-W1.8-LS3.7-RD; LCSC C5120763
Q10, Q11, Q13, Q15, Q16, Q18: Q_PNP_BEC; SOT-23-3_L2.9-W1.3-P1.90-LS2.4-BR; LCSC C2891805
Q12, Q14, Q17: Q_NPN_BEC; SOT-23; LCSC C5249680
R13, R14, R15, R16, R17, R18, R21, R22, R23, R24, R25, R26, R28, R29, R30, R31, R32, R33: 10K; R_0402_1005Metric; LCSC C102759
R19, R20, R27: 100K; R_0402_1005Metric; LCSC C3017514

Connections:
+3V3: C9.1, C10.1, C11.1, R13.1, R14.1, R16.1, R18.1, R21.1, R22.1, R24.1, R26.1, R28.1, R29.1, R31.1, R33.1; also elsewhere on the board
/HPD_A: D1.1 (K), Q12.3 (C), R18.2; also elsewhere on the board
/HPD_B: D2.1 (K), Q14.3 (C), R22.2; also elsewhere on the board
/HPD_C: D3.1 (K), Q17.3 (C), R29.2; also elsewhere on the board
/HPD_IN_A: R15.2, R16.2; also elsewhere on the board
/HPD_IN_B: R25.2, R26.2; also elsewhere on the board
/HPD_IN_C: R32.2, R33.2; also elsewhere on the board
/HPD_SELV_TRIP/HPD_IN: D4.2 (A), D5.2 (A), D6.2 (A); also elsewhere on the board
GND: Q12.2 (E), Q14.2 (E), Q17.2 (E); also elsewhere on the board
unnamed: C9.2, D1.2 (A), R19.1
unnamed: C10.2, D2.2 (A), R20.1
unnamed: C11.2, D3.2 (A), R27.1
unnamed: D4.1 (K), Q13.1 (B), R20.2
unnamed: D5.1 (K), Q10.1 (B), R19.2
unnamed: D6.1 (K), Q16.1 (B), R27.2
unnamed: Q10.3 (C), Q11.3 (C), R17.2
unnamed: Q10.2 (E), R13.2
unnamed: Q11.1 (B), R15.1
unnamed: Q11.2 (E), R14.2
unnamed: Q12.1 (B), R17.1
unnamed: Q13.3 (C), Q15.3 (C), R23.2
unnamed: Q13.2 (E), R21.2
unnamed: Q14.1 (B), R23.1
unnamed: Q15.1 (B), R25.1
unnamed: Q15.2 (E), R24.2
unnamed: Q16.3 (C), Q18.3 (C), R30.2
unnamed: Q16.2 (E), R28.2
unnamed: Q17.1 (B), R30.1
unnamed: Q18.1 (B), R32.1
unnamed: Q18.2 (E), R31.2

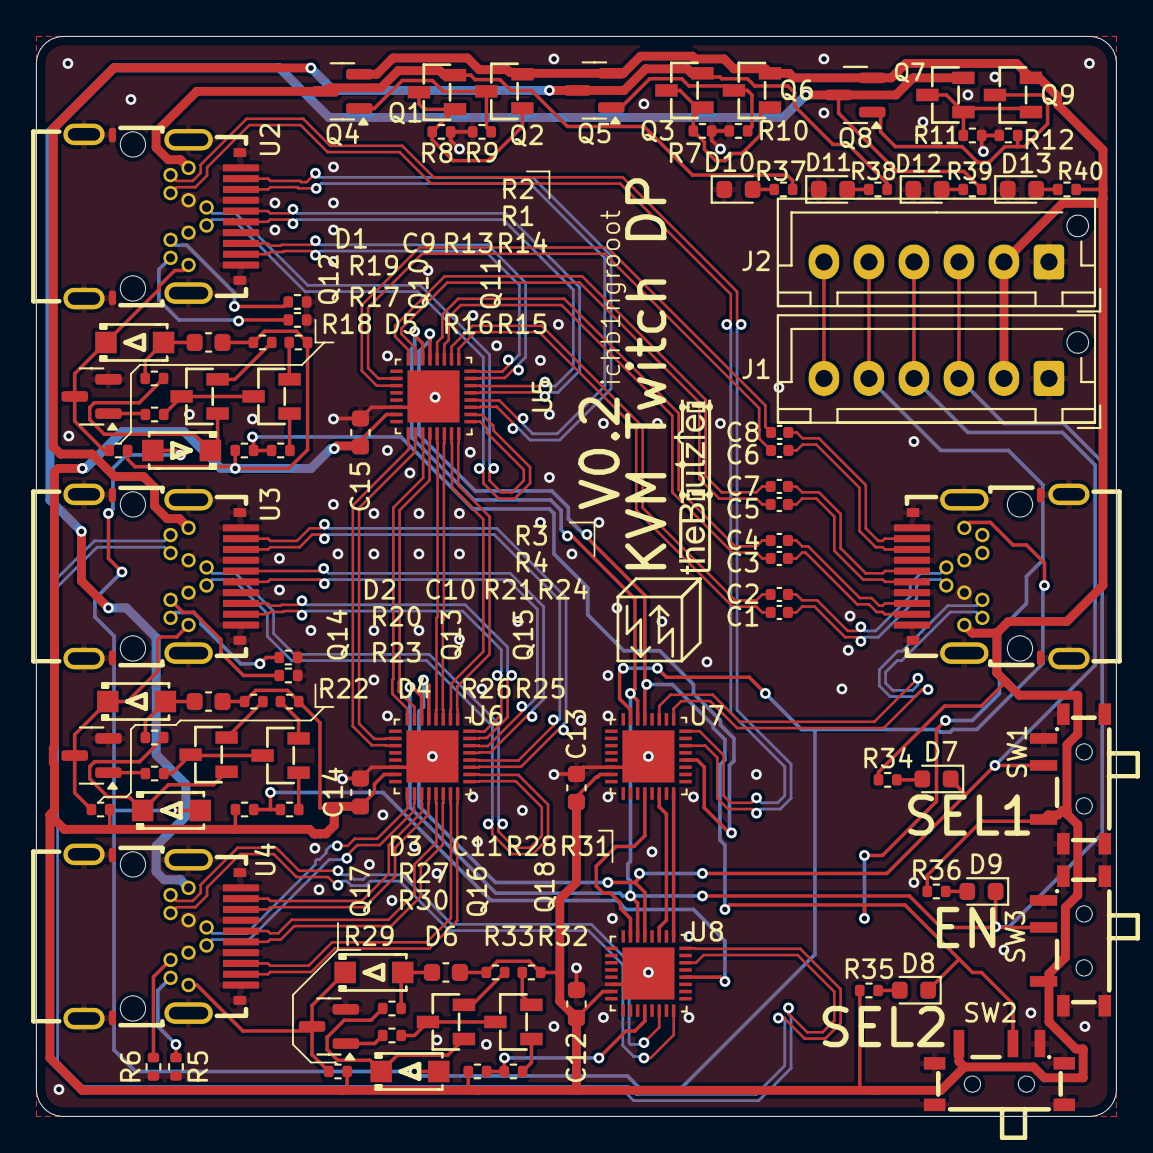
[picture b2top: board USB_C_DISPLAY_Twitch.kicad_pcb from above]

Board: 4 copper layers, 60.0 x 60.0 mm, 100 parts (0 on the bottom side), 114 nets.

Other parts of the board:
SM3: SYM_Arrow45_Tiny; Symbol_kurzschlussblog

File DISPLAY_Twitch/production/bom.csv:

Designator,Footprint,Quantity,Value,LCSC Part #
"C1, C2, C3, C4, C5, C6, C7, C8",0402,8,100n,C344189
"C10, C11, C12, C13, C14, C15, C9",0603,7,10u,C6119842
"D1, D2, D3, D4, D5, D6",SOD-123FL_L2.8-W1.8-LS3.7-RD,6,D,C5120763
"D10, D11, D12, D13, D7, D8, D9",0603,7,LED,C7496819
"J1, J2",JST_XH_B6B-XH-AM_1x06_P2.50mm_Vertical,2,Conn_01x06_Pin,C144397
"Q1, Q10, Q11, Q13, Q15, Q16, Q18, Q2, Q3, Q6, Q7, Q9",SOT-23-3_L2.9-W1.3-P1.90-LS2.4-BR,12,Q_PNP_BEC,C2891805
"Q12, Q14, Q17",SOT-23,3,Q_NPN_BEC,C5249680
"Q4, Q5, Q8",SOT-23,3,Q_PMOS_GSD,C41384537
"R1, R2, R3, R4, R5, R6",0402,6,5MEG,C3017614
"R10, R11, R12, R13, R14, R15, R16, R17, R18, R21, R22, R23, R24, R25, R26, R28, R29, R30, R31, R32, R33, R34, R35, R36, R37, R38, R39, R40, R7, R8, R9",0402,31,10K,C102759
"R19, R20, R27",0402,3,100K,C3017514
SM3,Symbol_kurzschlussblog,1,SYM_Arrow45_Tiny,
"SW1, SW2, SW3",SW-TH_MSK12C02,3,MSK12C02,C431540
"U1, U2, U3, U4",CONN-SMD_3VM11201-D730-7H,4,3VM11201-D730-7H,C2895506
"U5, U6, U7, U8",QFN-32_L4.0-W4.0-P0.40-TL-EP2.9,4,FSW3820YQFN32G/TR,C32713321
